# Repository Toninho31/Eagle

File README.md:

# Eagle

All my personal Eagle designs  - Any use of this repo without **Antoine Bonnet** express consent is prohibited !

Repository Contents
-------------------
* **/sch** - Drawing files
* **/brd** - Routing files
* **/cam** - Job files to output your design files
* **/dru** - Design rules
* **/scr** - Scripts for assigning keyboard shortcuts, grid sizes and layer colors
* **/ulp** - Commonly used user language programs for BOM generation and library export

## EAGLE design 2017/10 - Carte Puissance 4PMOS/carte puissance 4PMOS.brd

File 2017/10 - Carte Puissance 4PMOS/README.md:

Carte de puissance 
4 sorties PMOS FDD4141 (50A)

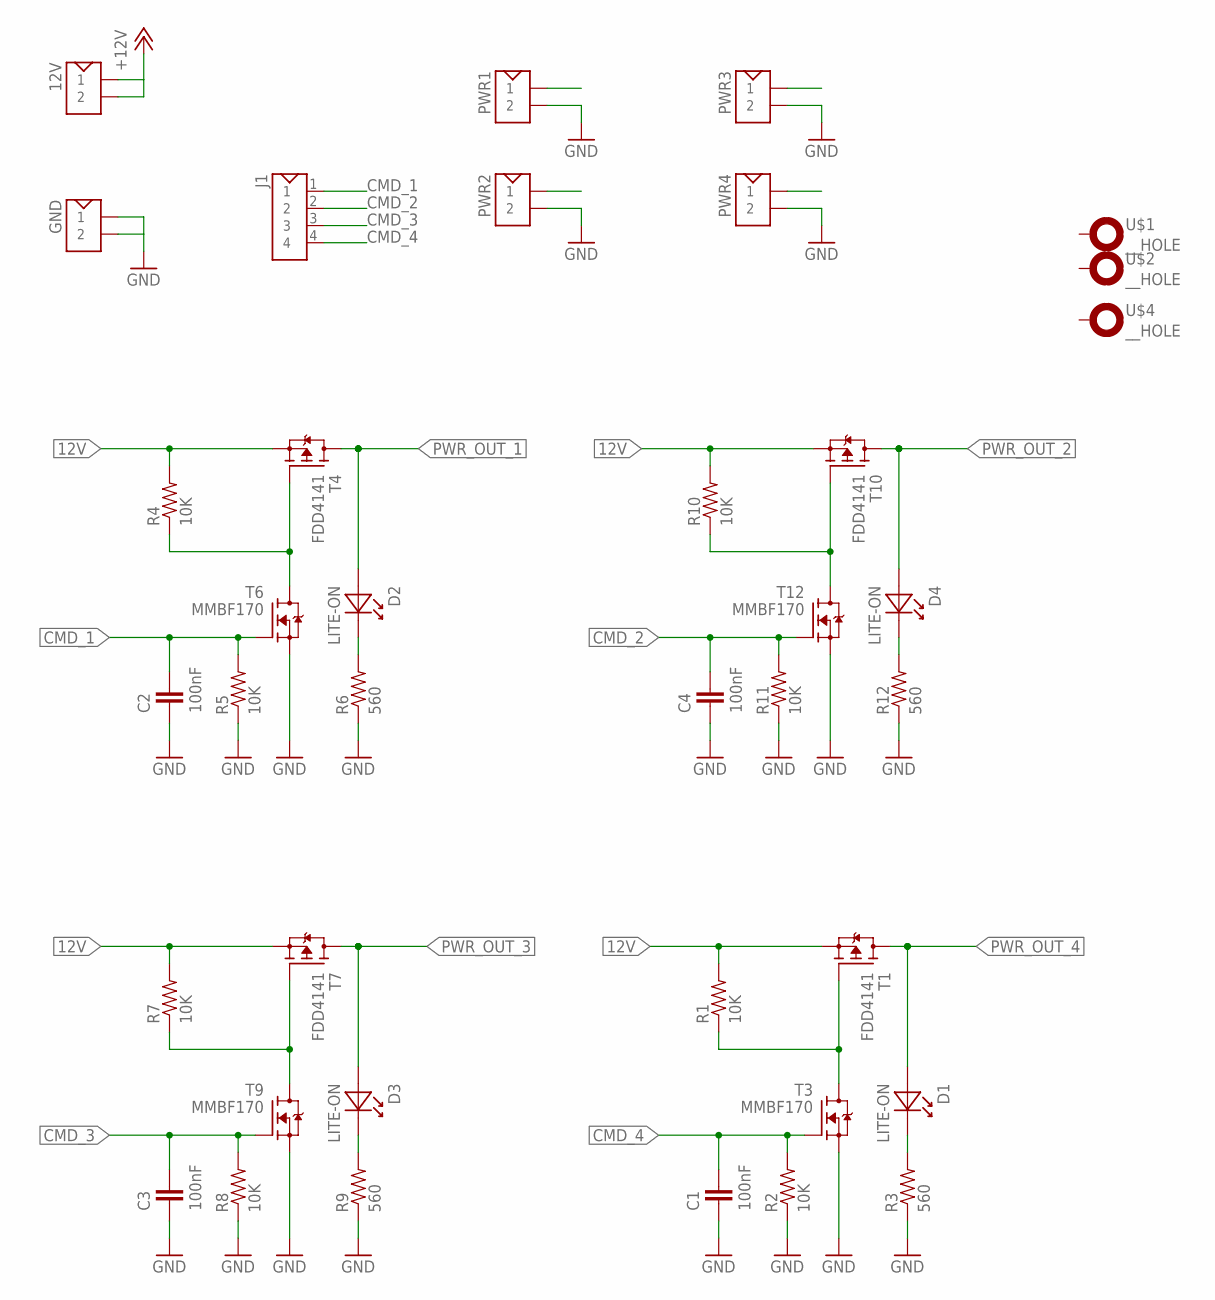
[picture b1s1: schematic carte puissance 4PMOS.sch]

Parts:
12V: CON_2_BORNIER_A; GMKDS_3_2-7.62
C1, C2, C3, C4: 100nF; 0805
D1, D2, D3, D4: LITE-ON; LITE-ON_LTST-C170
GND: CON_2_BORNIER_A; GMKDS_3_2-7.62
J1: CON_4_JST; B04B-XASK-1
PWR1, PWR2, PWR3, PWR4: CON_2_RS-PRO; 8971262
R1, R2, R4, R5, R7, R8, R10, R11: 10K; 0805
R3, R6, R9, R12: 560; 0805
T1, T4, T7, T10: FDD4141; D-PAC
T3, T6, T9, T12: MMBF170; SOT23
U$1, U$2, U$4: __HOLE

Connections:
12V: 12V.P$1 (1), 12V.P$2 (2), R1.2, R4.2, R7.2, R10.2, T1.3 (S), T4.3 (S), T7.3 (S), T10.3 (S)
CMD_1: C2.1, J1.1, R5.2, T6.1 (G)
CMD_2: C4.1, J1.2, R11.2, T12.1 (G)
CMD_3: C3.1, J1.3, R8.2, T9.1 (G)
CMD_4: C1.1, J1.4, R2.2, T3.1 (G)
GND: C1.2, C2.2, C3.2, C4.2, GND.P$1 (1), GND.P$2 (2), PWR1.2, PWR2.2, PWR3.2, PWR4.2, R2.1, R3.1, R5.1, R6.1, R8.1, R9.1, R11.1, R12.1, T3.2 (S), T6.2 (S), T9.2 (S), T12.2 (S)
unnamed: R1.1, T1.1 (G), T3.3 (D)
unnamed: D1.2 (CATODE), R3.2
unnamed: R4.1, T4.1 (G), T6.3 (D)
unnamed: R7.1, T7.1 (G), T9.3 (D)
unnamed: D3.2 (CATODE), R9.2
unnamed: D2.2 (CATODE), R6.2
unnamed: R10.1, T10.1 (G), T12.3 (D)
unnamed: D4.2 (CATODE), R12.2
PWR_OUT_1: D2.1 (ANODE), PWR1.1, T4.4 (D)
PWR_OUT_2: D4.1 (ANODE), PWR2.1, T10.4 (D)
PWR_OUT_3: D3.1 (ANODE), PWR3.1, T7.4 (D)
PWR_OUT_4: D1.1 (ANODE), PWR4.1, T1.4 (D)

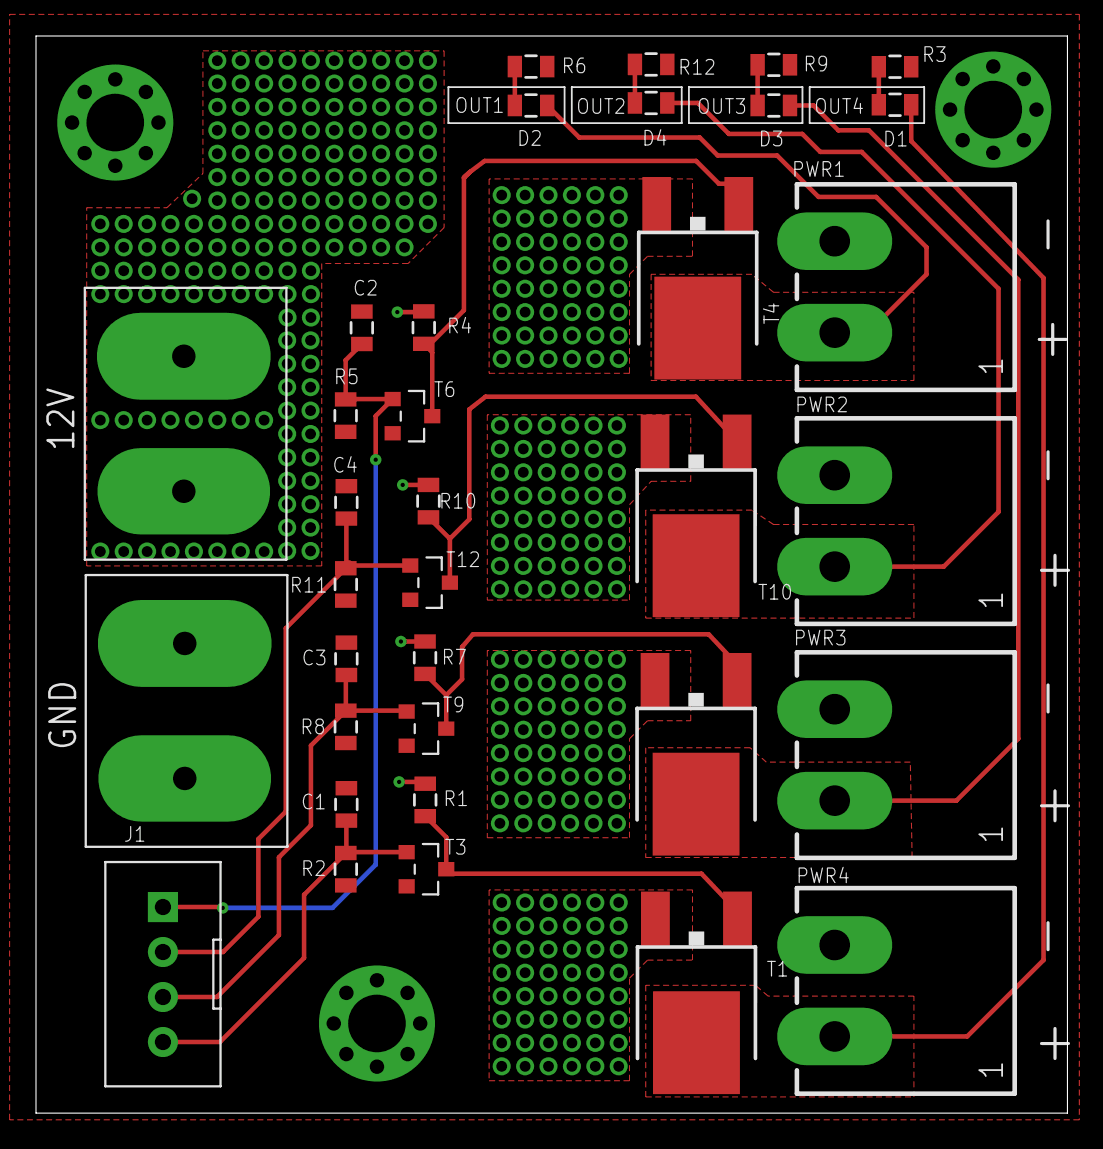
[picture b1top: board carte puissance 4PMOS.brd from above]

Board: 2 copper layers, 57.3 x 59.8 mm, 38 parts (0 on the bottom side), 18 nets.

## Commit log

2018-10-10 Create 2017

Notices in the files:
parts and their libraries:
SparkFun: Licensing: CC v3.0 Share-Alike You are welcome to use this library for commercial purposes.
